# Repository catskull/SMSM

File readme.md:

# SMSM
## A MIDI interface for the Sega Master System

Originally developed by [little-scale](http://little-scale.blogspot.com/2012/12/how-to-build-sega-master-system-midi.html).

Updated and maintained by [catskull](http://catskull.net).

## Building the ROM
Install wla-dx. On OSX this is easily achieved using by using Homebrew. Simply call `brew install wla-dx` from a command line. If you get a linking error, run ```sudo chown -R `whoami`:admin /usr/local/bin` and then run `brew link wla-dx```. If that completed successfully, run `wla-z80` from the command line and you should see something like this:

```
WLA Z80 Macro Assembler v9.9
Written by Ville Helin in 1998-2008 - In GitHub since 2014: https://github.com/vhelin/wla-dx
$VER: WLA-Z80 9.9 (15.8.2019)

USAGE: wla-z80 [OPTIONS] <ASM FILE>

Options:
-i  Add list file information
-M  Output makefile rules
-q  Quiet
-t  Test compile
-v  Verbose messages
-x  Extra compile time labels & definitions
-I [DIR]  Include directory
-D [DEF]  Declare definition

Output types:
-o [FILE]  Output object file
-l [FILE]  Output library file

EXAMPLE: wla-z80 -v -o main.obj main.asm
```

Congratulations! You're now ready to build the ROM!

cd into the ROM directory. Inside there is SMSM.asm, and build.sh. Enter `./build.sh` from the command line and it will build the ROM for you! You should now see a file called output.sms in this directory. This is the rom! Fire up your favorite emulator and give it a shot!

## ROM improvements

The ROM as developed by little-scale works quite well but is very bare bones. For example, it does not display anything on the screen when booted so there's no way of knowing whether or not your cartridge even works or not!

Here is a list of improvements I've made to the ROM so far:
 - clear the bios screen on boot
 - display a message on boot "System ready!"

Wish list:
 - mGB style console based interface for editing instrument presets (currently that is only supported by MIDI CC commands)
 - Implement the reset button on the console to reset the rom (a sort of MIDI panic)
 - Display a message if the YM2413 FM sound chip is detected

# Hardware

The hardware as developed by little-scale is quite complete. It does most of the heavy lifting, which is why the console ROM is so bare bones.

Here is a list of improvements I have made:
 - Added a status LED on pin 13. It blinks in a pattern and then goes steady on on first boot. Once notes are being sent, it blinks each time a note is received.
 - Added a MIDI panic button. Pressing it will kill all notes on the console.
 - I have designed a small PCB based around the Arduino Pro Mini for easiest use.

Wish list:
 - Currently, the PCB does not work with a Game Gear. It simply does not power on. Powering the unit externally does not work either. It powers on, but will not receive any MIDI data.
 - The PCB interface does not work with my cheapie USB MIDI cable. It will occasionally get midi data, but not reliably and will frequently miss MIDI note off.

# Credits
Sebastian Tomczak (aka little-scale) for the ROM, arduino code, and everything else.

Maxim for a great hello world tutorial.

Everyone at smspower.org

# License

little-scale released this with this note:

"The code etc for this is open and free to use. Please do not commercialise this. It is not for making money. It is for making cool chiptune musics. I encourage you to build one of these. It is easy and shouldn't take long. I encourage you to hack the code and play and have fun with it."

This is not really a valid software license. The ROM is based on Maxim's hello world program which also was not really released with a license.

For the time being, the code is somewhere in between public domain and all rights reserved. All contributions I make will be licensed under GPL v2.

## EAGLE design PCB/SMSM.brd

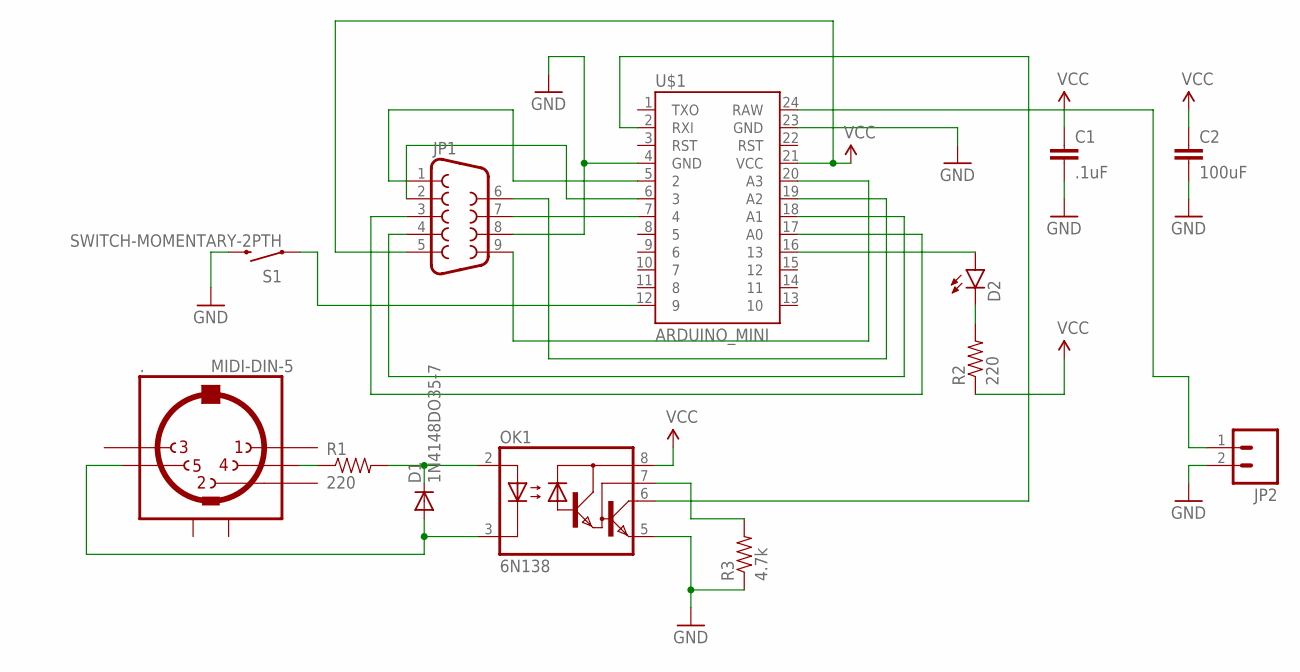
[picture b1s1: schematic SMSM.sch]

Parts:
.: MIDI-DIN-5
C1: .1uF; CAP-PTH-SMALL-KIT
C2: 100uF; CAP-PTH-SMALL-KIT
D1: 1N4148DO35-7; DO35-7
D2: LED3MM
JP1: DB9FEMALE; DB9
JP2: M02LOCK_LONGPADS; 1X02_LOCK_LONGPADS
OK1: 6N138; DIL08
R1, R2: 220; AXIAL-0.3
R3: 4.7k; AXIAL-0.3
S1: SWITCH-MOMENTARY-2PTH; TACTILE-PTH
U$1: ARDUINO_MINI

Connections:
GND: C1.2, C2.2, JP1.8, JP2.2, OK1.5 (GND), R3.P$1 (1), S1.3 (2), U$1.4 (GND), U$1.23 (GND)
unnamed: JP1.1, U$1.5 (2)
unnamed: JP1.2, U$1.6 (3)
unnamed: JP1.7, U$1.7 (4)
unnamed: D2.A, U$1.16 (13)
unnamed: JP1.3, U$1.17 (A0)
unnamed: JP1.4, U$1.18 (A1)
unnamed: JP1.6, U$1.19 (A2)
unnamed: JP1.9, U$1.20 (A3)
unnamed: ..5, D1.A, OK1.3 (C)
unnamed: D1.C, OK1.2 (A), R1.P$2 (2)
unnamed: D2.K (C), R2.P$2 (2)
unnamed: ..4, R1.P$1 (1)
unnamed: OK1.7 (VB), R3.P$2 (2)
unnamed: OK1.6 (VO), U$1.2 (RXI)
unnamed: S1.1, U$1.12 (9)
unnamed: JP2.1, U$1.24 (RAW)
VCC: C1.1, C2.1, JP1.5, OK1.8 (VCC), R2.P$1 (1), U$1.21 (VCC)

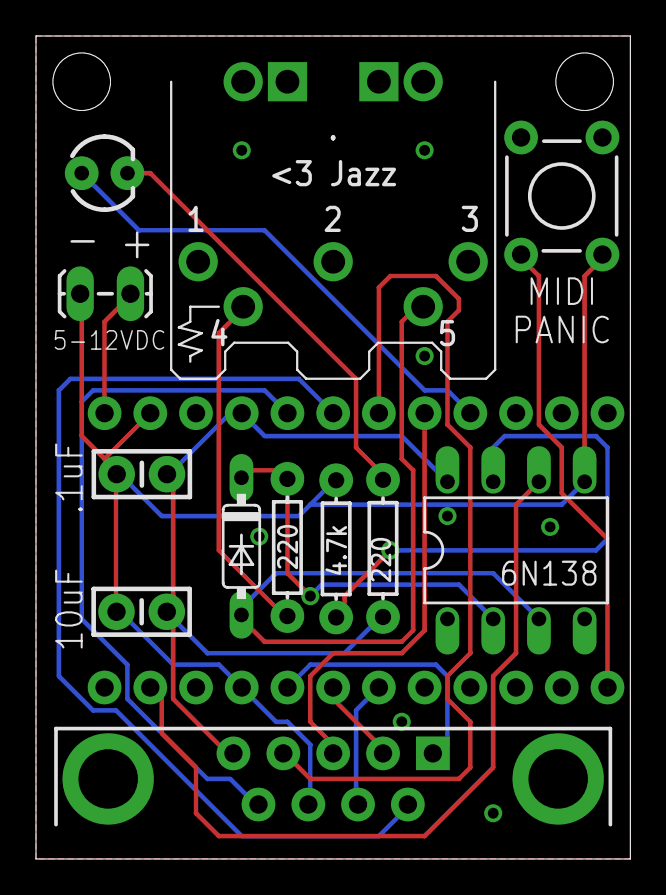
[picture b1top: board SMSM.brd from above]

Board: 2 copper layers, 33.0 x 45.7 mm, 13 parts (0 on the bottom side), 18 nets.

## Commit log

2016-05-16 Add midi panic button
2016-05-16 Add status led stuff
2016-05-16 Use .asm extension for rom instead of .txt
2016-05-16 Move all console code to ROM directory
2016-05-16 Add script for building the rom
2016-05-16 Remove rom from repo
2016-05-16 Add a read
2016-05-16 Add updated by catskill
2016-05-16 Trim whitespace
2016-07-25 Add new rom?
2016-07-25 Add boards
2019-10-28 Smaller ROM banks
    ROM banks reduced to $2000, header will hopefully be located at $1FF0.
    Please re-compile and see where ROM header is. Test on hardware, not emulator.
2019-11-15 update binary
2019-11-15 Fix readme

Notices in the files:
parts and their libraries:
SparkFun-Connectors: Licensing: Creative Commons ShareAlike 4.0 International - https://creativecommons.org/licenses/by-sa/4.0
